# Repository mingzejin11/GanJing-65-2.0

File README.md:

# GanJing 65 rev 2.0
**A 65% keyboard with a rotary encoder, OLED screen and USB-c. Made using the Elite-c and through-hole components for easy soldering.**

[Bill of materials](https://octopart.com/bom-tool/jvwkTsDN)

## Layout options
The GanJing 65 PCB is hotswappable, supports ISO layouts, stepped caps lock, split right shift, and split spacebar options. There is also a soldered PCB available.

### Supported hotswap layouts

## Hotswap PCB layout
### Front

### Back

## Hotswap PCB layout with exposed traces
### Front ANSI

### Front ISO and split spacebar

### Back

### Supported solder layouts

## Solder PCB layout
### Front

### Front ISO and 7u spacebar

### Back

## Schematic

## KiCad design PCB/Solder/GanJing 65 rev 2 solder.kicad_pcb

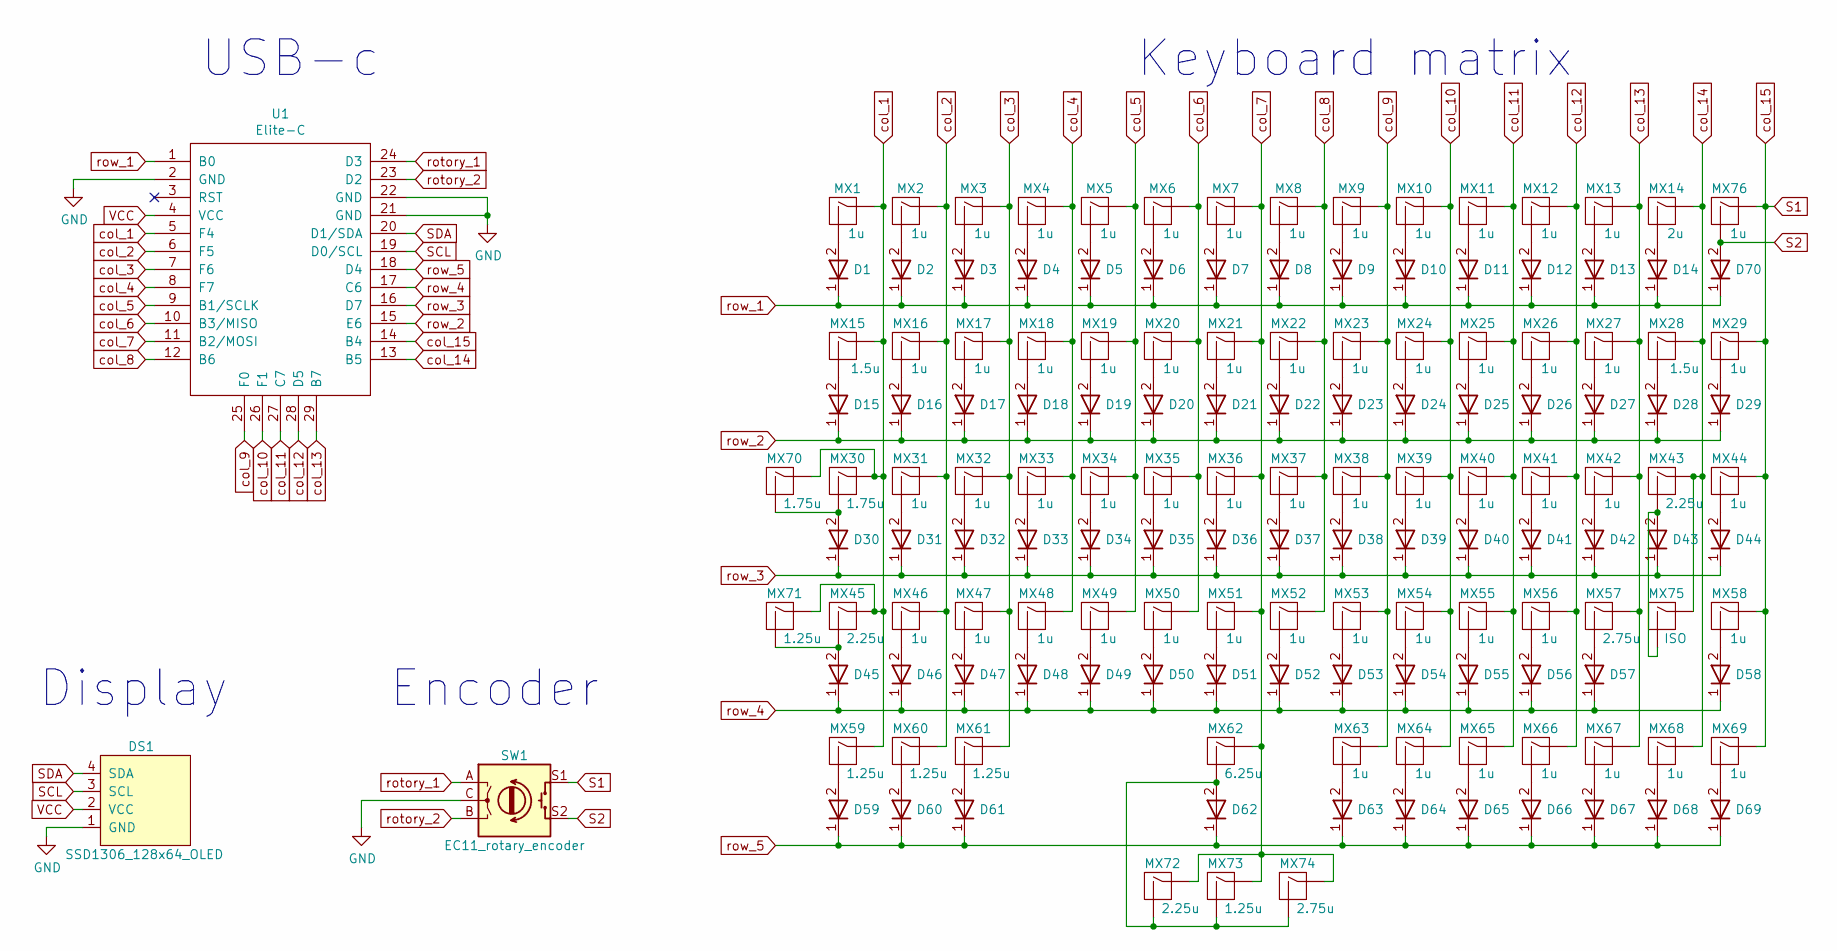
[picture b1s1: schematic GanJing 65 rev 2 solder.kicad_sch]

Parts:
D1, D2, D3, D4, D5, D6, D7, D8, D9, D10, D11, D12, D13, D14, D15, D16, D17, D18, D19, D20, D21, D22, D23, D24, D25, D26, D27, D28, D29, D30, D31, D32, D33, D34, D35, D36, D37, D38, D39, D40, D41, D42, D43, D44, D45, D46, D47, D48, D49, D50, D51, D52, D53, D54, D55, D56, D57, D58, D59, D60, D61, D62, D63, D64, D65, D66, D67, D68, D69, D70: 1N4148TR_diode
DS1: SSD1306_128x64_OLED
MX1, MX2, MX3, MX4, MX5, MX6, MX7, MX8, MX9, MX10, MX11, MX12, MX13, MX16, MX17, MX18, MX19, MX20, MX21, MX22, MX23, MX24, MX25, MX26, MX27, MX29, MX31, MX32, MX33, MX34, MX35, MX36, MX37, MX38, MX39, MX40, MX41, MX42, MX44, MX46, MX47, MX48, MX49, MX50, MX51, MX52, MX53, MX54, MX55, MX56, MX58, MX63, MX64, MX65, MX66, MX67, MX68, MX69, MX76: MX_1u_no_LED
MX14: MX_2u_no_LED
MX15, MX28: MX_1.5u_no_LED
MX30: MX_1.75u_no_LED
MX43, MX45: MX_2.25u_no_LED
MX57: MX_2.75u_no_LED
MX59, MX60, MX61, MX71, MX73: MX_1.25u_no_LED
MX62: MX_6.25u_no_LED_flipped_stabs
MX70: MX_1.75u_stepped_no_LED
MX72: MX_2.25u_no_LED_flipped_stabs
MX74: MX_2.75u_no_LED_flipped_stabs
MX75: MX_ISO_no_LED_flipped_stabs
SW1: EC11_rotary_encoder
U1: Elite-C

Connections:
GND: DS1.1 (GND), SW1.C, U1.2 (GND), U1.21 (GND), U1.22 (GND); also elsewhere on the board
unnamed: D1.2, MX1.2 (ROW)
unnamed: D2.2, MX2.2 (ROW)
unnamed: D3.2, MX3.2 (ROW)
unnamed: D4.2, MX4.2 (ROW)
unnamed: D5.2, MX5.2 (ROW)
unnamed: D6.2, MX6.2 (ROW)
unnamed: D7.2, MX7.2 (ROW)
unnamed: D8.2, MX8.2 (ROW)
unnamed: D9.2, MX9.2 (ROW)
unnamed: D10.2, MX10.2 (ROW)
unnamed: D11.2, MX11.2 (ROW)
unnamed: D12.2, MX12.2 (ROW)
unnamed: D13.2, MX13.2 (ROW)
unnamed: D14.2, MX14.2 (ROW)
unnamed: D15.2, MX15.2 (ROW)
unnamed: D16.2, MX16.2 (ROW)
unnamed: D17.2, MX17.2 (ROW)
unnamed: D18.2, MX18.2 (ROW)
unnamed: D19.2, MX19.2 (ROW)
unnamed: D20.2, MX20.2 (ROW)
unnamed: D21.2, MX21.2 (ROW)
unnamed: D22.2, MX22.2 (ROW)
unnamed: D23.2, MX23.2 (ROW)
unnamed: D24.2, MX24.2 (ROW)
unnamed: D25.2, MX25.2 (ROW)
unnamed: D26.2, MX26.2 (ROW)
unnamed: D27.2, MX27.2 (ROW)
unnamed: D28.2, MX28.2 (ROW)
unnamed: D29.2, MX29.2 (ROW)
unnamed: D30.2, MX30.2 (ROW), MX70.2 (ROW)
unnamed: D31.2, MX31.2 (ROW)
unnamed: D32.2, MX32.2 (ROW)
unnamed: D33.2, MX33.2 (ROW)
unnamed: D34.2, MX34.2 (ROW)
unnamed: D35.2, MX35.2 (ROW)
unnamed: D36.2, MX36.2 (ROW)
unnamed: D37.2, MX37.2 (ROW)
unnamed: D38.2, MX38.2 (ROW)
unnamed: D39.2, MX39.2 (ROW)
unnamed: D40.2, MX40.2 (ROW)
unnamed: D41.2, MX41.2 (ROW)
unnamed: D42.2, MX42.2 (ROW)
unnamed: D43.2, MX43.2 (ROW), MX75.2 (ROW)
unnamed: D44.2, MX44.2 (ROW)
unnamed: D45.2, MX45.2 (ROW), MX71.2 (ROW)
unnamed: D46.2, MX46.2 (ROW)
unnamed: D47.2, MX47.2 (ROW)
unnamed: D48.2, MX48.2 (ROW)
unnamed: D49.2, MX49.2 (ROW)
unnamed: D50.2, MX50.2 (ROW)
unnamed: D51.2, MX51.2 (ROW)
unnamed: D52.2, MX52.2 (ROW)
unnamed: D53.2, MX53.2 (ROW)
unnamed: D54.2, MX54.2 (ROW)
unnamed: D55.2, MX55.2 (ROW)
unnamed: D56.2, MX56.2 (ROW)
unnamed: D57.2, MX57.2 (ROW)
unnamed: D58.2, MX58.2 (ROW)
unnamed: D59.2, MX59.2 (ROW)
unnamed: D60.2, MX60.2 (ROW)
unnamed: D61.2, MX61.2 (ROW)
unnamed: D62.2, MX62.2 (ROW), MX72.2 (ROW), MX73.2 (ROW), MX74.2 (ROW)
unnamed: D63.2, MX63.2 (ROW)
unnamed: D64.2, MX64.2 (ROW)
unnamed: D65.2, MX65.2 (ROW)
unnamed: D66.2, MX66.2 (ROW)
unnamed: D67.2, MX67.2 (ROW)
unnamed: D68.2, MX68.2 (ROW)
unnamed: D69.2, MX69.2 (ROW)
S1: MX29.1 (COL), MX44.1 (COL), MX58.1 (COL), MX69.1 (COL), MX76.1 (COL), SW1.S1, U1.14 (B4); also elsewhere on the board
S2: D70.2, MX76.2 (ROW), SW1.S2; also elsewhere on the board
SCL: DS1.3 (SCL), U1.19 (D0/SCL)
SDA: DS1.4 (SDA), U1.20 (D1/SDA)
VCC: DS1.2 (VCC), U1.4 (VCC)
col_1: MX1.1 (COL), MX15.1 (COL), MX30.1 (COL), MX45.1 (COL), MX59.1 (COL), MX70.1 (COL), MX71.1 (COL), U1.5 (F4)
col_2: MX2.1 (COL), MX16.1 (COL), MX31.1 (COL), MX46.1 (COL), MX60.1 (COL), U1.6 (F5)
col_3: MX3.1 (COL), MX17.1 (COL), MX32.1 (COL), MX47.1 (COL), MX61.1 (COL), U1.7 (F6)
col_4: MX4.1 (COL), MX18.1 (COL), MX33.1 (COL), MX48.1 (COL), U1.8 (F7)
col_5: MX5.1 (COL), MX19.1 (COL), MX34.1 (COL), MX49.1 (COL), U1.9 (B1/SCLK)
col_6: MX6.1 (COL), MX20.1 (COL), MX35.1 (COL), MX50.1 (COL), U1.10 (B3/MISO)
col_7: MX7.1 (COL), MX21.1 (COL), MX36.1 (COL), MX51.1 (COL), MX62.1 (COL), MX72.1 (COL), MX73.1 (COL), MX74.1 (COL), U1.11 (B2/MOSI)
col_8: MX8.1 (COL), MX22.1 (COL), MX37.1 (COL), MX52.1 (COL), U1.12 (B6)
col_9: MX9.1 (COL), MX23.1 (COL), MX38.1 (COL), MX53.1 (COL), MX63.1 (COL), U1.25 (F0)
col_10: MX10.1 (COL), MX24.1 (COL), MX39.1 (COL), MX54.1 (COL), MX64.1 (COL), U1.26 (F1)
col_11: MX11.1 (COL), MX25.1 (COL), MX40.1 (COL), MX55.1 (COL), MX65.1 (COL), U1.27 (C7)
col_12: MX12.1 (COL), MX26.1 (COL), MX41.1 (COL), MX56.1 (COL), MX66.1 (COL), U1.28 (D5)
col_13: MX13.1 (COL), MX27.1 (COL), MX42.1 (COL), MX57.1 (COL), MX67.1 (COL), U1.29 (B7)
col_14: MX14.1 (COL), MX28.1 (COL), MX43.1 (COL), MX68.1 (COL), MX75.1 (COL), U1.13 (B5)
rotory_1: SW1.A, U1.24 (D3); also elsewhere on the board
rotory_2: SW1.B, U1.23 (D2); also elsewhere on the board
row_1: D1.1, D2.1, D3.1, D4.1, D5.1, D6.1, D7.1, D8.1, D9.1, D10.1, D11.1, D12.1, D13.1, D14.1, D70.1, U1.1 (B0)
row_2: D15.1, D16.1, D17.1, D18.1, D19.1, D20.1, D21.1, D22.1, D23.1, D24.1, D25.1, D26.1, D27.1, D28.1, D29.1, U1.15 (E6)
row_3: D30.1, D31.1, D32.1, D33.1, D34.1, D35.1, D36.1, D37.1, D38.1, D39.1, D40.1, D41.1, D42.1, D43.1, D44.1, U1.16 (D7)
row_4: D45.1, D46.1, D47.1, D48.1, D49.1, D50.1, D51.1, D52.1, D53.1, D54.1, D55.1, D56.1, D57.1, D58.1, U1.17 (C6)
row_5: D59.1, D60.1, D61.1, D62.1, D63.1, D64.1, D65.1, D66.1, D67.1, D68.1, D69.1, U1.18 (D4)

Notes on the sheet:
Keyboard matrix
Display
USB-c
Encoder

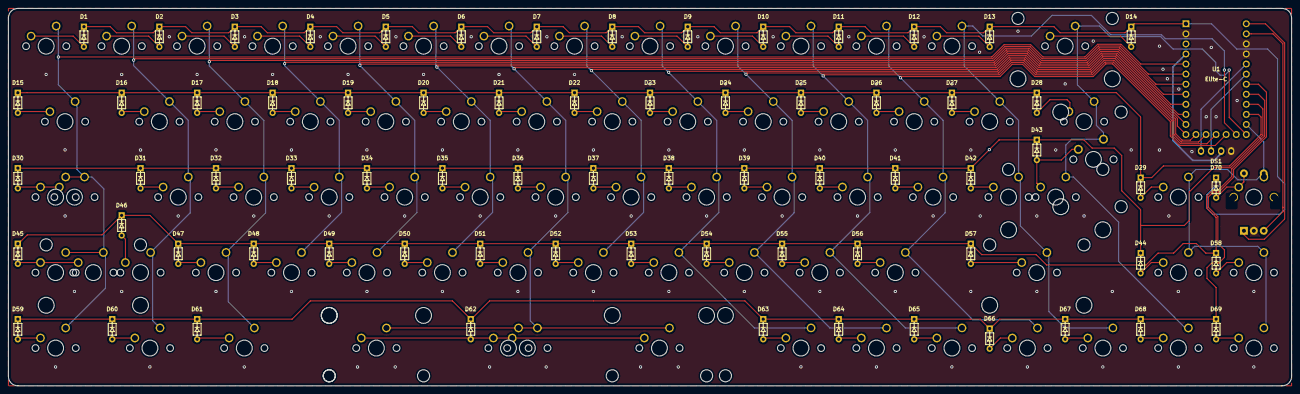
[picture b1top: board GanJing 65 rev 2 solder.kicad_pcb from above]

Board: 2 copper layers, 323.8 x 95.2 mm, 149 parts (0 on the bottom side), 96 nets.

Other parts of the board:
SWe: EC11_rotary_encoder

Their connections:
GND: SWe.C; also elsewhere on the board
S1: SWe.S1; also elsewhere on the board
S2: SWe.S2; also elsewhere on the board
rotory_1: SWe.A; also elsewhere on the board
rotory_2: SWe.B; also elsewhere on the board

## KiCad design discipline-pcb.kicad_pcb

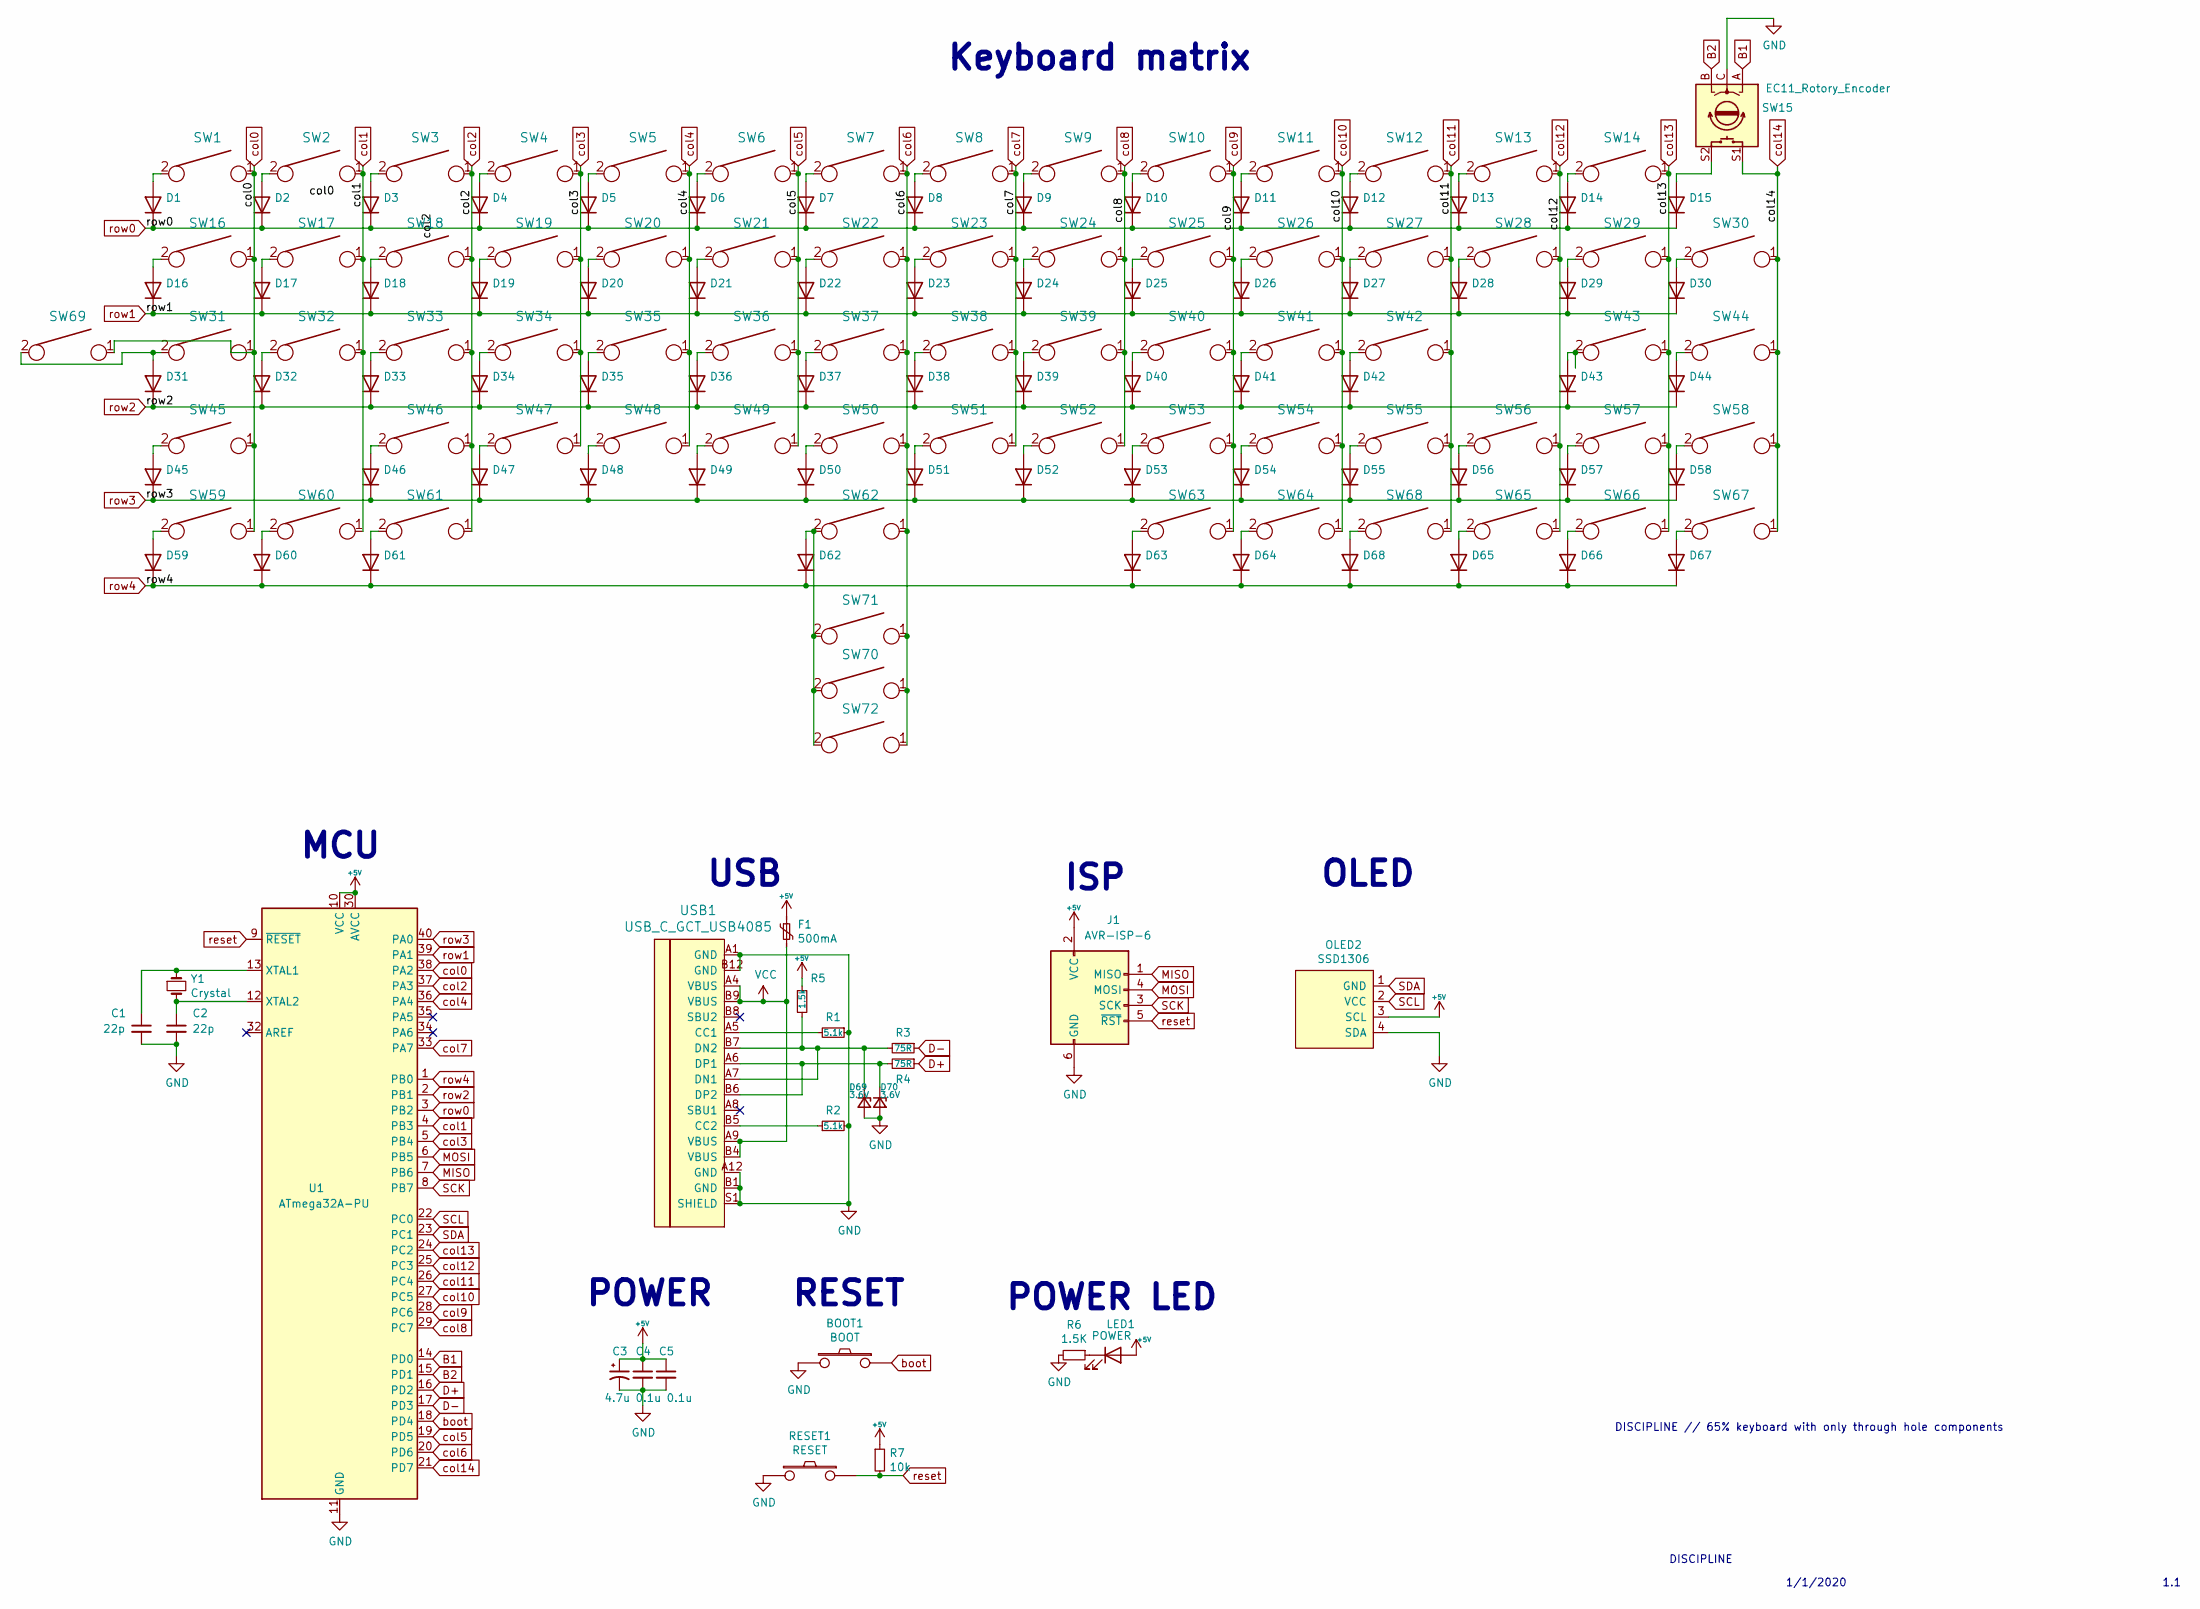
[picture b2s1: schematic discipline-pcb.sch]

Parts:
BOOT1: BOOT; SW_PUSH_6mm
C1, C2: 22p; C_Disc_D3.0mm_W1.6mm_P2.50mm
C3: 4.7u; CP_Radial_D4.0mm_P1.50mm
C4, C5: 0.1u; C_Disc_D4.3mm_W1.9mm_P5.00mm
D1, D2, D3, D4, D5, D6, D7, D8, D9, D10, D11, D12, D13, D14, D15, D16, D17, D18, D19, D20, D21, D22, D23, D24, D25, D26, D27, D28, D29, D30, D31, D32, D33, D34, D35, D36, D37, D38, D39, D40, D41, D42, D43, D44, D45, D46, D47, D48, D49, D50, D51, D52, D53, D54, D55, D56, D57, D58, D59, D60, D61, D62, D63, D64, D65, D66, D67, D68: D_DO-35_SOD27_P5.08mm_Horizontal
D69, D70: 3.6V; D_DO-35_SOD27_P5.08mm_Horizontal
F1: 500mA; polyfuse_5.1mm
J1: AVR-ISP-6; AVR_ICSP_3x2
LED1: POWER; LED_D3.0mm
OLED2: SSD1306; 128x64OLED
R1, R2: 5.1k; R_Axial_DIN0204_L3.6mm_D1.6mm_P5.08mm_Horizontal
R3, R4: 75R; R_Axial_DIN0204_L3.6mm_D1.6mm_P5.08mm_Horizontal
R5: 1.5k; R_Axial_DIN0204_L3.6mm_D1.6mm_P5.08mm_Horizontal
R6: 1.5K; R_Axial_DIN0204_L3.6mm_D1.6mm_P5.08mm_Horizontal
R7: 10k; R_Axial_DIN0204_L3.6mm_D1.6mm_P5.08mm_Horizontal
RESET1: RESET; SW_PUSH_6mm
SW1, SW2, SW3, SW4, SW5, SW6, SW7, SW8, SW9, SW10, SW11, SW12, SW13, SW17, SW18, SW19, SW20, SW21, SW22, SW23, SW24, SW25, SW26, SW27, SW28, SW30, SW32, SW33, SW34, SW35, SW36, SW37, SW38, SW39, SW40, SW41, SW42, SW44, SW46, SW47, SW48, SW49, SW50, SW51, SW52, SW53, SW54, SW55, SW57, SW58, SW63, SW64, SW65, SW66, SW67, SW68: KEYSW; SW_Cherry_MX1A_1.00u_PCB-NOSCREEN
SW14: KEYSW; SW_Cherry_MX1A_2.00u_PCBNOSCREEN
SW15: EC11_Rotory_Encoder; RotaryEncoder_Alps_EC11E-Switch_Vertical_H20mm
SW16, SW29: KEYSW; SW_Cherry_MX1A_1.50u_PCBNOSCREEN
SW31, SW56: KEYSW; SW_Cherry_MX1A_1.75u_PCBNOSCREEN
SW43, SW45: KEYSW; SW_Cherry_MX1A_2.25u_PCBNOSCREEN
SW59, SW60, SW61: KEYSW; SW_Cherry_MX1A_1.25u_PCBNOSCREEN
SW62: KEYSW; MXOnly-6.25U-ReversedStabilizers-NoLED
SW69: KEYSW; MXOnly-1.75U-Stepped-NoLED
SW70: KEYSW; MXOnly-2.25U-ReversedStabilizers-NoLED
SW71: KEYSW; MXOnly-1.25U-NoLED
SW72: KEYSW; MXOnly-2.75U-ReversedStabilizers-NoLED
U1: ATmega32A-PU; DIP-40_W15.24mm
USB1: USB_C_GCT_USB4085
Y1: Crystal; Crystal_HC49-4H_Vertical

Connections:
+5V: C3.1, C4.1, C5.1, F1.1, J1.2 (VCC), LED1.2 (A), OLED2.3 (SCL), R5.1, R7.1, U1.10 (VCC), U1.30 (AVCC)
B1: SW15.A, U1.14 (PD0)
B2: SW15.B, U1.15 (PD1)
D+: R4.1, U1.16 (PD2)
D-: R3.1, U1.17 (PD3)
GND: BOOT1.1, C1.2, C2.2, C3.2, C4.2, C5.2, D69.2 (A), D70.2 (A), J1.6 (GND), OLED2.4 (SDA), R1.1, R2.2, R6.2, RESET1.1, SW15.C, U1.11 (GND), U1.31 (GND), USB1.A1 (GND), USB1.A12 (GND), USB1.B1 (GND), USB1.B12 (GND), USB1.S1 (SHIELD)
MISO: J1.1 (MISO), U1.7 (PB6)
MOSI: J1.4 (MOSI), U1.6 (PB5)
unnamed: C1.1, U1.13 (XTAL1), Y1.1
unnamed: C2.1, U1.12 (XTAL2), Y1.2
unnamed: D1.2 (A), SW1.2
unnamed: D2.2 (A), SW2.2
unnamed: D3.2 (A), SW3.2
unnamed: D4.2 (A), SW4.2
unnamed: D5.2 (A), SW5.2
unnamed: D6.2 (A), SW6.2
unnamed: D7.2 (A), SW7.2
unnamed: D8.2 (A), SW8.2
unnamed: D9.2 (A), SW9.2
unnamed: D10.2 (A), SW10.2
unnamed: D11.2 (A), SW11.2
unnamed: D12.2 (A), SW12.2
unnamed: D13.2 (A), SW13.2
unnamed: D14.2 (A), SW14.2
unnamed: D15.2 (A), SW15.S2
unnamed: D16.2 (A), SW16.2
unnamed: D17.2 (A), SW17.2
unnamed: D18.2 (A), SW18.2
unnamed: D19.2 (A), SW19.2
unnamed: D20.2 (A), SW20.2
unnamed: D21.2 (A), SW21.2
unnamed: D22.2 (A), SW22.2
unnamed: D23.2 (A), SW23.2
unnamed: D24.2 (A), SW24.2
unnamed: D25.2 (A), SW25.2
unnamed: D26.2 (A), SW26.2
unnamed: D27.2 (A), SW27.2
unnamed: D28.2 (A), SW28.2
unnamed: D29.2 (A), SW29.2
unnamed: D30.2 (A), SW30.2
unnamed: D31.2 (A), SW31.2, SW69.2
unnamed: D32.2 (A), SW32.2
unnamed: D33.2 (A), SW33.2
unnamed: D34.2 (A), SW34.2
unnamed: D35.2 (A), SW35.2
unnamed: D36.2 (A), SW36.2
unnamed: D37.2 (A), SW37.2
unnamed: D38.2 (A), SW38.2
unnamed: D39.2 (A), SW39.2
unnamed: D40.2 (A), SW40.2
unnamed: D41.2 (A), SW41.2
unnamed: D42.2 (A), SW42.2
unnamed: D43.2 (A), SW43.2
unnamed: D44.2 (A), SW44.2
unnamed: D45.2 (A), SW45.2
unnamed: D46.2 (A), SW46.2
unnamed: D47.2 (A), SW47.2
unnamed: D48.2 (A), SW48.2
unnamed: D49.2 (A), SW49.2
unnamed: D50.2 (A), SW50.2
unnamed: D51.2 (A), SW51.2
unnamed: D52.2 (A), SW52.2
unnamed: D53.2 (A), SW53.2
unnamed: D54.2 (A), SW54.2
unnamed: D55.2 (A), SW55.2
unnamed: D56.2 (A), SW56.2
unnamed: D57.2 (A), SW57.2
unnamed: D58.2 (A), SW58.2
unnamed: D59.2 (A), SW59.2
unnamed: D60.2 (A), SW60.2
unnamed: D61.2 (A), SW61.2
unnamed: D62.2 (A), SW62.2, SW70.2, SW71.2, SW72.2
unnamed: D63.2 (A), SW63.2
unnamed: D64.2 (A), SW64.2
unnamed: D65.2 (A), SW65.2
unnamed: D66.2 (A), SW66.2
unnamed: D67.2 (A), SW67.2
unnamed: D68.2 (A), SW68.2
unnamed: D69.1 (K), R3.2, R5.2, USB1.A7 (DN1), USB1.B7 (DN2)
unnamed: D70.1 (K), R4.2, USB1.A6 (DP1), USB1.B6 (DP2)
unnamed: LED1.1 (K), R6.1
unnamed: R1.2, USB1.A5 (CC1)
unnamed: R2.1, USB1.B5 (CC2)
SCK: J1.3 (SCK), U1.8 (PB7)
SCL: OLED2.2 (VCC), U1.22 (PC0)
SDA: OLED2.1 (GND), U1.23 (PC1)
VCC: F1.2, USB1.A4 (VBUS), USB1.A9 (VBUS), USB1.B4 (VBUS), USB1.B9 (VBUS)
boot: BOOT1.2, U1.18 (PD4)
col0: SW1.1, SW16.1, SW31.1, SW45.1, SW59.1, SW69.1, U1.38 (PA2)
col1: SW2.1, SW17.1, SW32.1, SW60.1, U1.4 (PB3)
col2: SW3.1, SW18.1, SW33.1, SW46.1, SW61.1, U1.37 (PA3)
col3: SW4.1, SW19.1, SW34.1, SW47.1, U1.5 (PB4)
col4: SW5.1, SW20.1, SW35.1, SW48.1, U1.36 (PA4)
col5: SW6.1, SW21.1, SW36.1, SW49.1, U1.19 (PD5)
col6: SW7.1, SW22.1, SW37.1, SW50.1, SW62.1, SW70.1, SW71.1, SW72.1, U1.20 (PD6)
col7: SW8.1, SW23.1, SW38.1, SW51.1, U1.33 (PA7)
col8: SW9.1, SW24.1, SW39.1, SW52.1, U1.29 (PC7)
col9: SW10.1, SW25.1, SW40.1, SW53.1, SW63.1, U1.28 (PC6)
col10: SW11.1, SW26.1, SW41.1, SW54.1, SW64.1, U1.27 (PC5)
col11: SW12.1, SW27.1, SW42.1, SW55.1, SW68.1, U1.26 (PC4)
col12: SW13.1, SW28.1, SW56.1, SW65.1, U1.25 (PC3)
col13: SW14.1, SW29.1, SW43.1, SW57.1, SW66.1, U1.24 (PC2)
col14: SW15.S1, SW30.1, SW44.1, SW58.1, SW67.1, U1.21 (PD7)
reset: J1.5 (~RST), R7.2, RESET1.2, U1.9 (~RESET)
row0: D1.1 (K), D2.1 (K), D3.1 (K), D4.1 (K), D5.1 (K), D6.1 (K), D7.1 (K), D8.1 (K), D9.1 (K), D10.1 (K), D11.1 (K), D12.1 (K), D13.1 (K), D14.1 (K), D15.1 (K), U1.3 (PB2)
row1: D16.1 (K), D17.1 (K), D18.1 (K), D19.1 (K), D20.1 (K), D21.1 (K), D22.1 (K), D23.1 (K), D24.1 (K), D25.1 (K), D26.1 (K), D27.1 (K), D28.1 (K), D29.1 (K), D30.1 (K), U1.39 (PA1)
row2: D31.1 (K), D32.1 (K), D33.1 (K), D34.1 (K), D35.1 (K), D36.1 (K), D37.1 (K), D38.1 (K), D39.1 (K), D40.1 (K), D41.1 (K), D42.1 (K), D43.1 (K), D44.1 (K), U1.2 (PB1)
row3: D45.1 (K), D46.1 (K), D47.1 (K), D48.1 (K), D49.1 (K), D50.1 (K), D51.1 (K), D52.1 (K), D53.1 (K), D54.1 (K), D55.1 (K), D56.1 (K), D57.1 (K), D58.1 (K), U1.40 (PA0)
row4: D59.1 (K), D60.1 (K), D61.1 (K), D62.1 (K), D63.1 (K), D64.1 (K), D65.1 (K), D66.1 (K), D67.1 (K), D68.1 (K), U1.1 (PB0)

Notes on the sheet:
DISCIPLINE // 65% keyboard with only through hole components
1/1/2020
DISCIPLINE
1.1
USB
ISP
POWER
RESET
POWER LED
Keyboard matrix
OLED
MCU

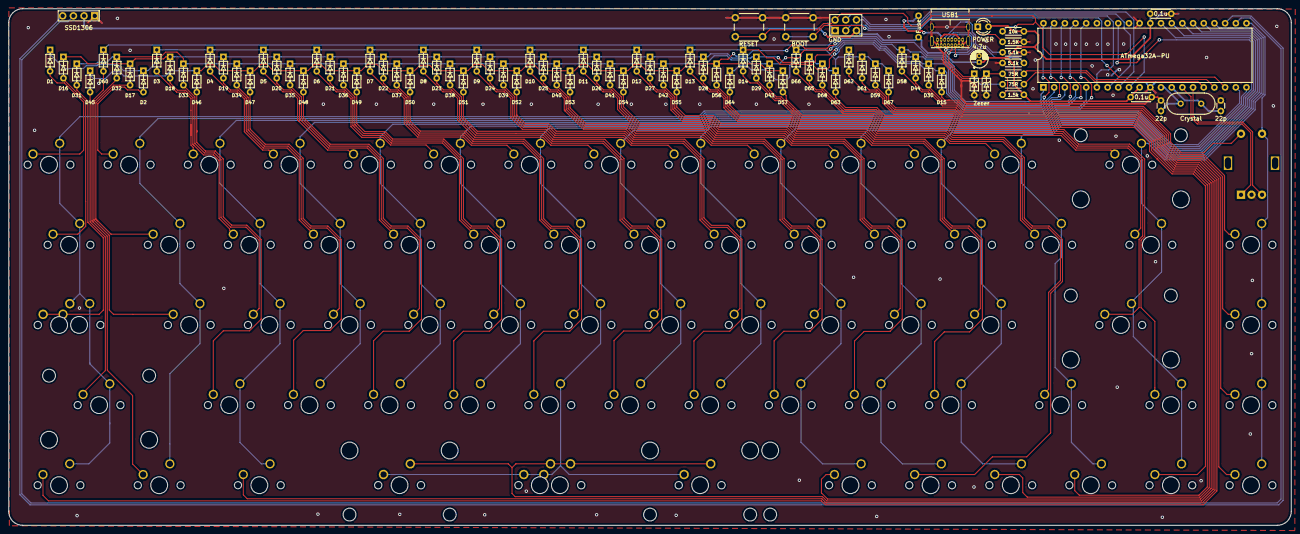
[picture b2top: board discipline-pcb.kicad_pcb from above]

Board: 2 copper layers, 304.9 x 122.8 mm, 164 parts (0 on the bottom side), 109 nets.

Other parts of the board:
L***: LOGO; GanJing logo

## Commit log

2021-11-21 Initial placement
2021-11-25 Initial routing
2021-12-04 Finished routing
2021-12-05 Adding images and optional key switch instead of rotory knob
2021-12-05 Cleaning up some routing
2021-12-05 adding README
2021-12-05 Renaming images
2021-12-05 Changing F mask cuz I'm a dumbass lol
2021-12-05 Updating images
2021-12-05 werw
2021-12-05 git is dumb
2021-12-05 Updating gerbers
2021-12-07 Created a hotswap version
2021-12-07 Adding new images
2021-12-07 new readme
2021-12-07 Updating README
2021-12-07 Adding firmware and case files
2021-12-14 Adding split spacebar to hotswap PCB
2021-12-19 Writing the firmware is fun
2021-12-21 finished firmware
2021-12-21 Fixing hotswap PCB traces
2021-12-21 updating hex files
2022-01-11 Updated PCBs to adjust the location of the encoder plus fix routing errors in the hotswap version. Plate file is also completed, case files still need to be finalized
2022-01-17 Updating firmware so animation doesn't play backwards
2022-01-19 Updating firmware to inclue a WPM counter
2022-01-19 Forgot to save a file lol
2022-01-24 Switching to KiCad 6.0.1 so some files have been converted and the component symbol library files has been converted from .lib to .kicad_sym
2022-01-26 Case files completed
2022-01-28 Updating plate file
2022-01-28 Adding extra screw hole for stability and fixing foot piece
2022-01-28 removing backup files
2022-01-31 Updating case to 10mm boarders
2022-02-04 Updating the CAD files to all be 0.00mm
2022-02-04 Fixing plate space bar
2022-02-08 Adding a bunch of different layout options to the hotswap board
2022-02-09 Updating plate tolerances
2022-02-20 Updating PCB and firmware
2022-02-27 Adding cutting files
2022-03-09 Adding new gasket strips
2022-03-31 Updating plate to support split shift key on the right side
2022-04-18 Adding 3d models and flipping the right shift stabilizers to reduce interference
2022-04-18 Adding option to have switch instead of knob
2022-04-19 Updating soldered version
2022-04-19 Updating top case file
2022-04-19 Changing folder name
2022-05-15 Updating gerbers and sodlered PCB
2022-05-15 updating soldered pcb to have logo graphic
2022-05-17 Making minor trace edits to all three versions of PCB
2022-05-17 Adding new layout images
2022-05-17 Adding 7u to soldered PCB
2022-05-17 Adding rounded pcbs
2022-08-19 Adding new firmware hex files
